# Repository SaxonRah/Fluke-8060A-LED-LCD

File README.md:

# Fluke 8060A LCD-to-LED Replacement Mod
## PCB for the Fluke 8060A's LCD but converted to LED.
### Inspired by Dmitri Faguet, ModemHead, ogdento, JdaleH, retiredcaps, DrTaylor, Dave and everyone else at EEVBlog.
Most work was done intermittently through 20/4/2023 - 8/2/2024. Finalized Rev 1 on 28/9/2024.

- The original PCB was made and it had 2 errors, layout of digits and missing pin 23.
-   I fixed both, rerouted the entire board and add the reuse of the original LCD elastomeric/zebra strip.

## Fluke 8060A is simply the best.
This is mostly a KiCAD project for the LED PCB, with some extra photos, PDFs, and various things related to the 8060A.

## Notes
Finalized the Rev 1 PCB. Will do BOM and assembly for PCBWay soon.

### 8060A LED Mod Rev 1

### Schematic

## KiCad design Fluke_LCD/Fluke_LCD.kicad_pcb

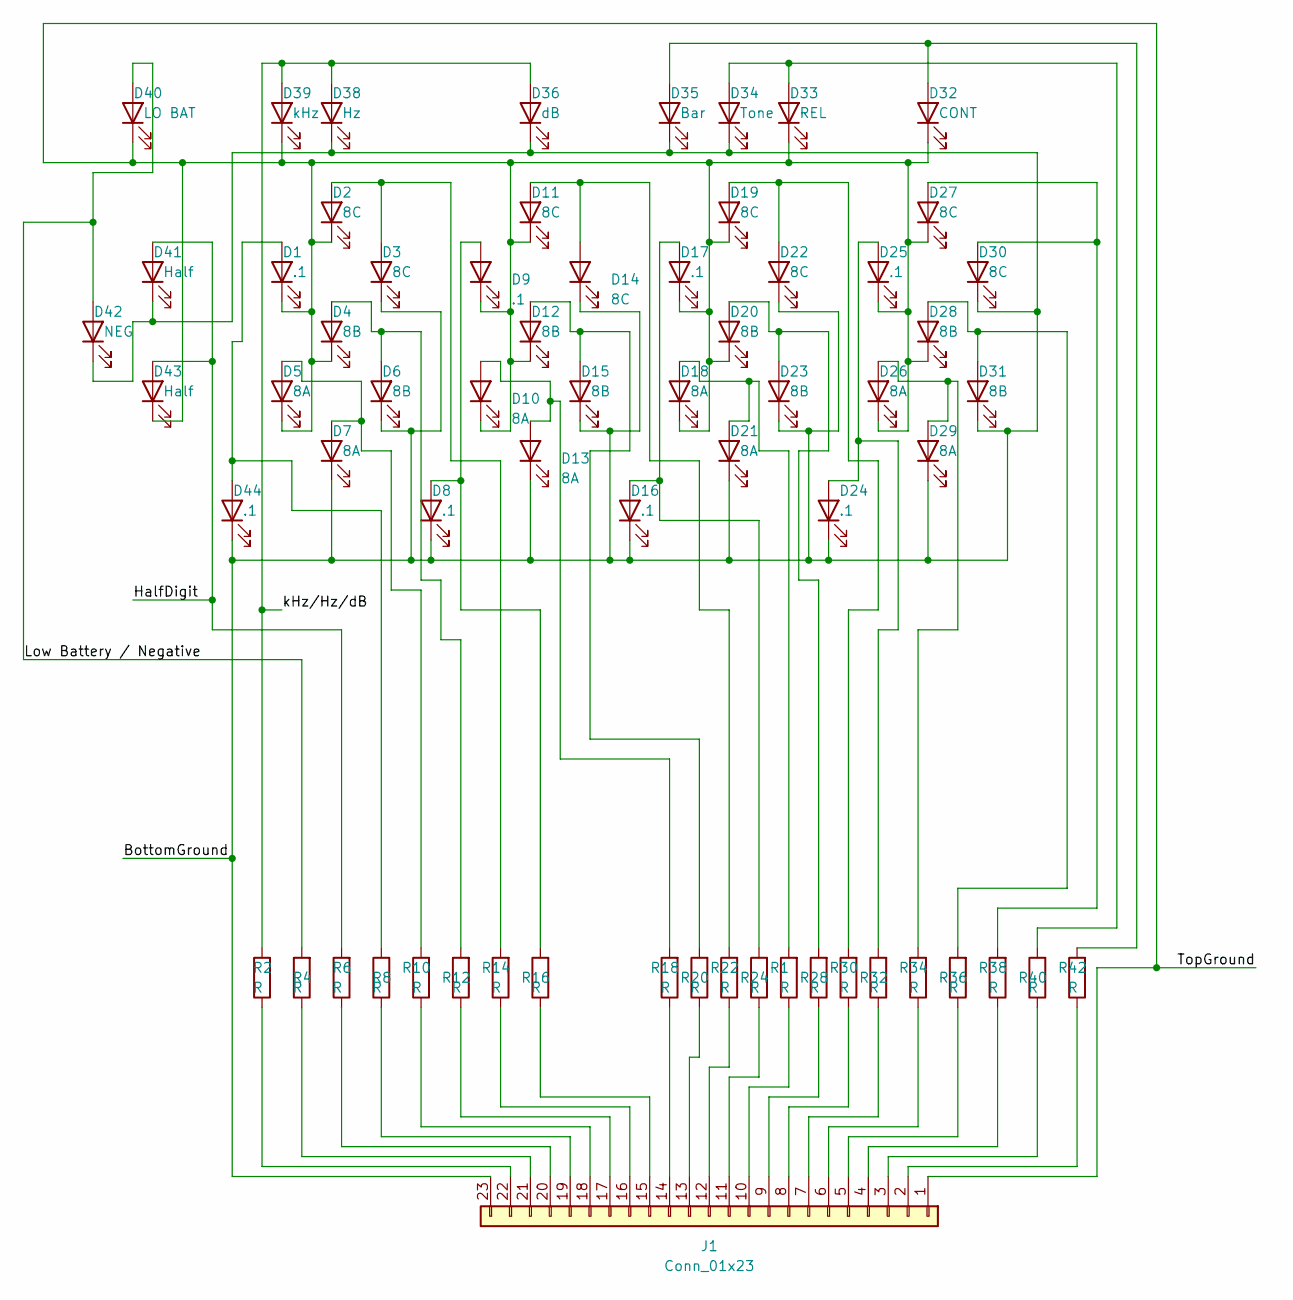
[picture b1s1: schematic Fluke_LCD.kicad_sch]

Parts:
D1, D8, D9, D16, D17, D24, D25, D44: .1; LED_0805_2012Metric_Pad1.3x1.40mm_HandSolder
D2, D3, D11, D14, D19, D22, D27, D30: 8C; LED_0805_2012Metric_Pad1.3x1.40mm_HandSolder
D4, D6, D12, D15, D20, D23, D28, D31: 8B; LED_0805_2012Metric_Pad1.3x1.40mm_HandSolder
D5, D7, D10, D13, D18, D21, D26, D29: 8A; LED_0805_2012Metric_Pad1.3x1.40mm_HandSolder
D32: CONT; LED_0805_2012Metric_Pad1.3x1.40mm_HandSolder
D33: REL; LED_0805_2012Metric_Pad1.3x1.40mm_HandSolder
D34: Tone; LED_0805_2012Metric_Pad1.3x1.40mm_HandSolder
D35: Bar; LED_0805_2012Metric_Pad1.3x1.40mm_HandSolder
D36: dB; LED_0805_2012Metric_Pad1.3x1.40mm_HandSolder
D38: Hz; LED_0805_2012Metric_Pad1.3x1.40mm_HandSolder
D39: kHz; LED_0805_2012Metric_Pad1.3x1.40mm_HandSolder
D40: LO BAT; LED_0805_2012Metric_Pad1.3x1.40mm_HandSolder
D41, D43: Half; LED_0805_2012Metric_Pad1.3x1.40mm_HandSolder
D42: NEG; LED_0805_2012Metric_Pad1.3x1.40mm_HandSolder
J1: Conn_01x23; Fluke_8060A_LCD_ElastoPads
R1, R2, R4, R6, R8, R10, R12, R14, R16, R18, R20, R22, R24, R28, R30, R32, R34, R36, R38, R40, R42: R; R_0805_2012Metric_Pad1.20x1.40mm_HandSolder

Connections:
/BottomGround: D3.1 (K), D6.1 (K), D7.1 (K), D8.1 (K), D13.1 (K), D14.1 (K), D15.1 (K), D16.1 (K), D21.1 (K), D22.1 (K), D23.1 (K), D24.1 (K), D29.1 (K), D30.1 (K), D31.1 (K), D34.1 (K), D35.1 (K), D36.1 (K), D38.1 (K), D41.1 (K), D42.1 (K), D44.1 (K), J1.23
/HalfDigit: D41.2 (A), D43.2 (A), R6.2
/Low Battery / Negative: D40.2 (A), D42.2 (A), R4.2
/TopGround: D1.1 (K), D2.1 (K), D4.1 (K), D5.1 (K), D9.1 (K), D10.1 (K), D11.1 (K), D12.1 (K), D17.1 (K), D18.1 (K), D19.1 (K), D20.1 (K), D25.1 (K), D26.1 (K), D27.1 (K), D28.1 (K), D32.1 (K), D33.1 (K), D39.1 (K), D40.1 (K), D43.1 (K), J1.1
/kHz/Hz/dB: D36.2 (A), D38.2 (A), D39.2 (A), R2.2
unnamed: D1.2 (A), D44.2 (A), R8.2
unnamed: D2.2 (A), D3.2 (A), R14.2
unnamed: D4.2 (A), D6.2 (A), R12.2
unnamed: D5.2 (A), D7.2 (A), R10.2
unnamed: D8.2 (A), D9.2 (A), R16.2
unnamed: D10.2 (A), D13.2 (A), R18.2
unnamed: D11.2 (A), D14.2 (A), R22.2
unnamed: D12.2 (A), D15.2 (A), R20.2
unnamed: D16.2 (A), D17.2 (A), R24.2
unnamed: D18.2 (A), D21.2 (A), R1.2
unnamed: D19.2 (A), D22.2 (A), R30.2
unnamed: D20.2 (A), D23.2 (A), R28.2
unnamed: D24.2 (A), D25.2 (A), R32.2
unnamed: D26.2 (A), D29.2 (A), R34.2
unnamed: D27.2 (A), D30.2 (A), R38.2
unnamed: D28.2 (A), D31.2 (A), R36.2
unnamed: D32.2 (A), D35.2 (A), R42.2
unnamed: D33.2 (A), D34.2 (A), R40.2
unnamed: J1.2, R42.1
unnamed: J1.3, R40.1
unnamed: J1.4, R38.1
unnamed: J1.5, R36.1
unnamed: J1.6, R34.1
unnamed: J1.7, R32.1
unnamed: J1.8, R30.1
unnamed: J1.9, R28.1
unnamed: J1.10, R1.1
unnamed: J1.11, R24.1
unnamed: J1.12, R22.1
unnamed: J1.13, R20.1
unnamed: J1.14, R18.1
unnamed: J1.15, R16.1
unnamed: J1.16, R14.1
unnamed: J1.17, R12.1
unnamed: J1.18, R10.1
unnamed: J1.19, R8.1
unnamed: J1.20, R6.1
unnamed: J1.21, R4.1
unnamed: J1.22, R2.1

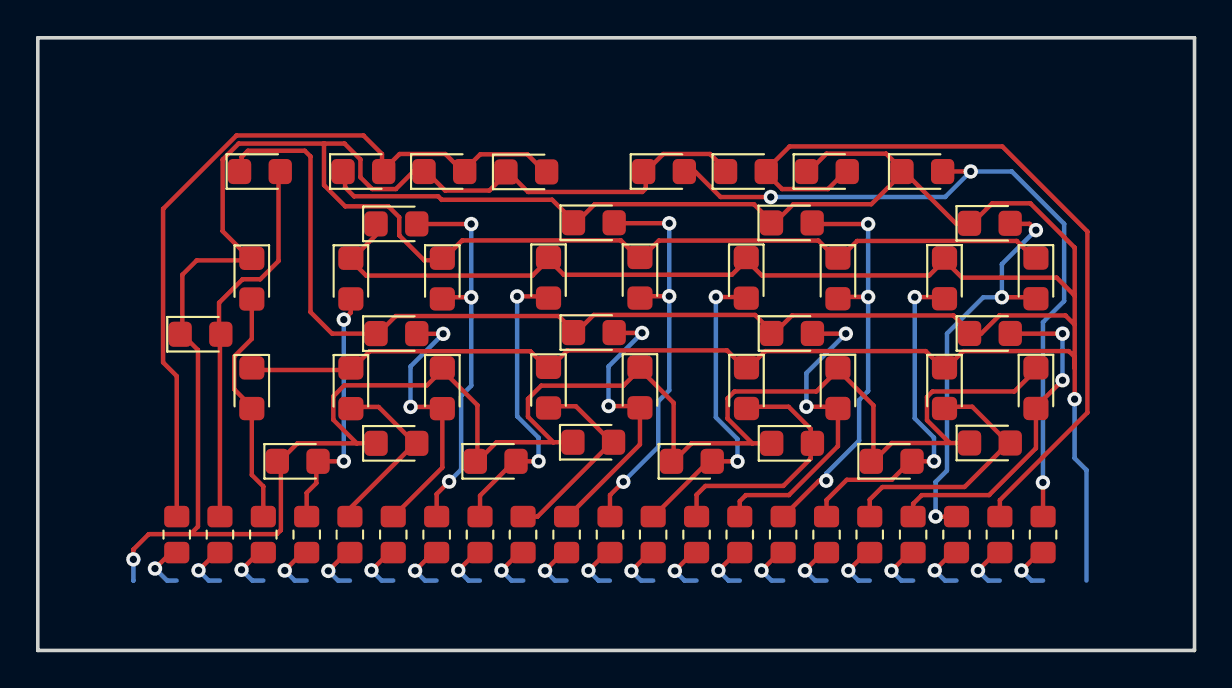
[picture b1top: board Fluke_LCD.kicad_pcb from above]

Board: 2 copper layers, 64.3 x 34.0 mm, 65 parts (0 on the bottom side), 44 nets.

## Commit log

2024-09-12 Initial commit.
    Everything I've collected and created for the Fluke 8060A
2024-09-12 Edit via sizes
2024-09-13 Add Schematic render
2024-09-13 Add Teardrops/Clean Traces on Fluke_LCD_d2mm
2024-09-27 A drop-in replacement now. Almost finished.
2024-09-29 Update libraries, positions, and footprints.
2024-09-29 8060A LED Mod Rev1
2024-10-14 add schematic
2024-10-14 Add ServiceUser Manuals
